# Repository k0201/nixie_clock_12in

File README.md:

# nixie_clock_12in
KiCad hardware project for IN12 lamps

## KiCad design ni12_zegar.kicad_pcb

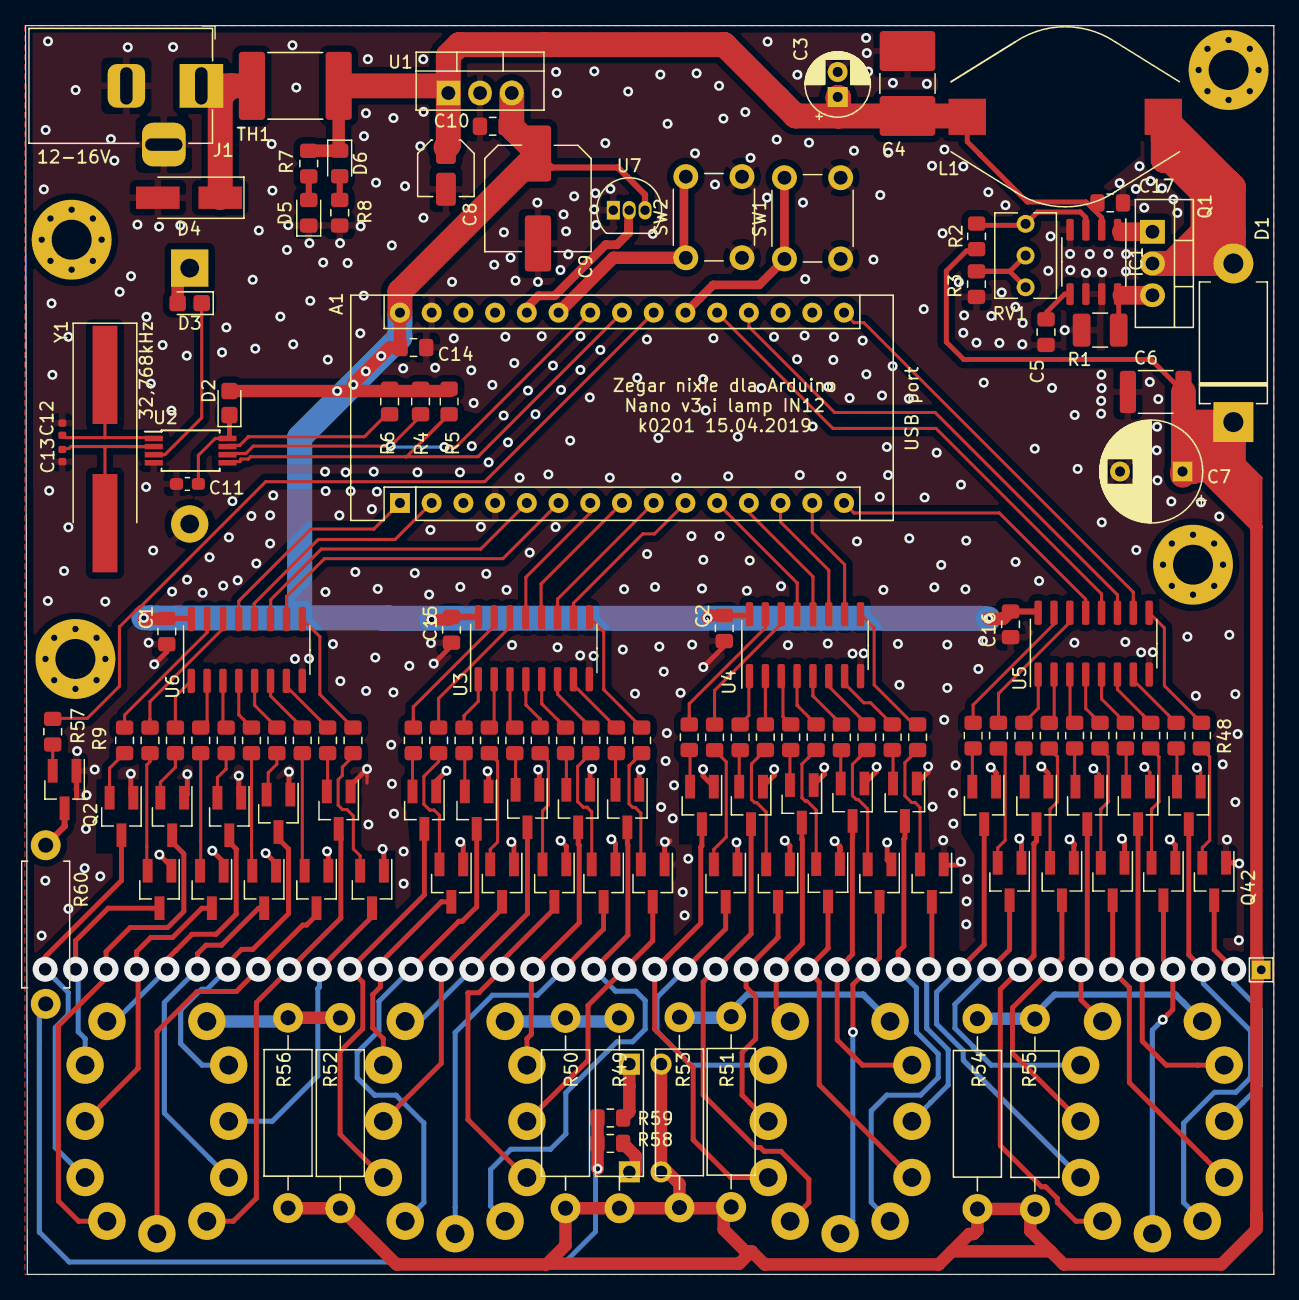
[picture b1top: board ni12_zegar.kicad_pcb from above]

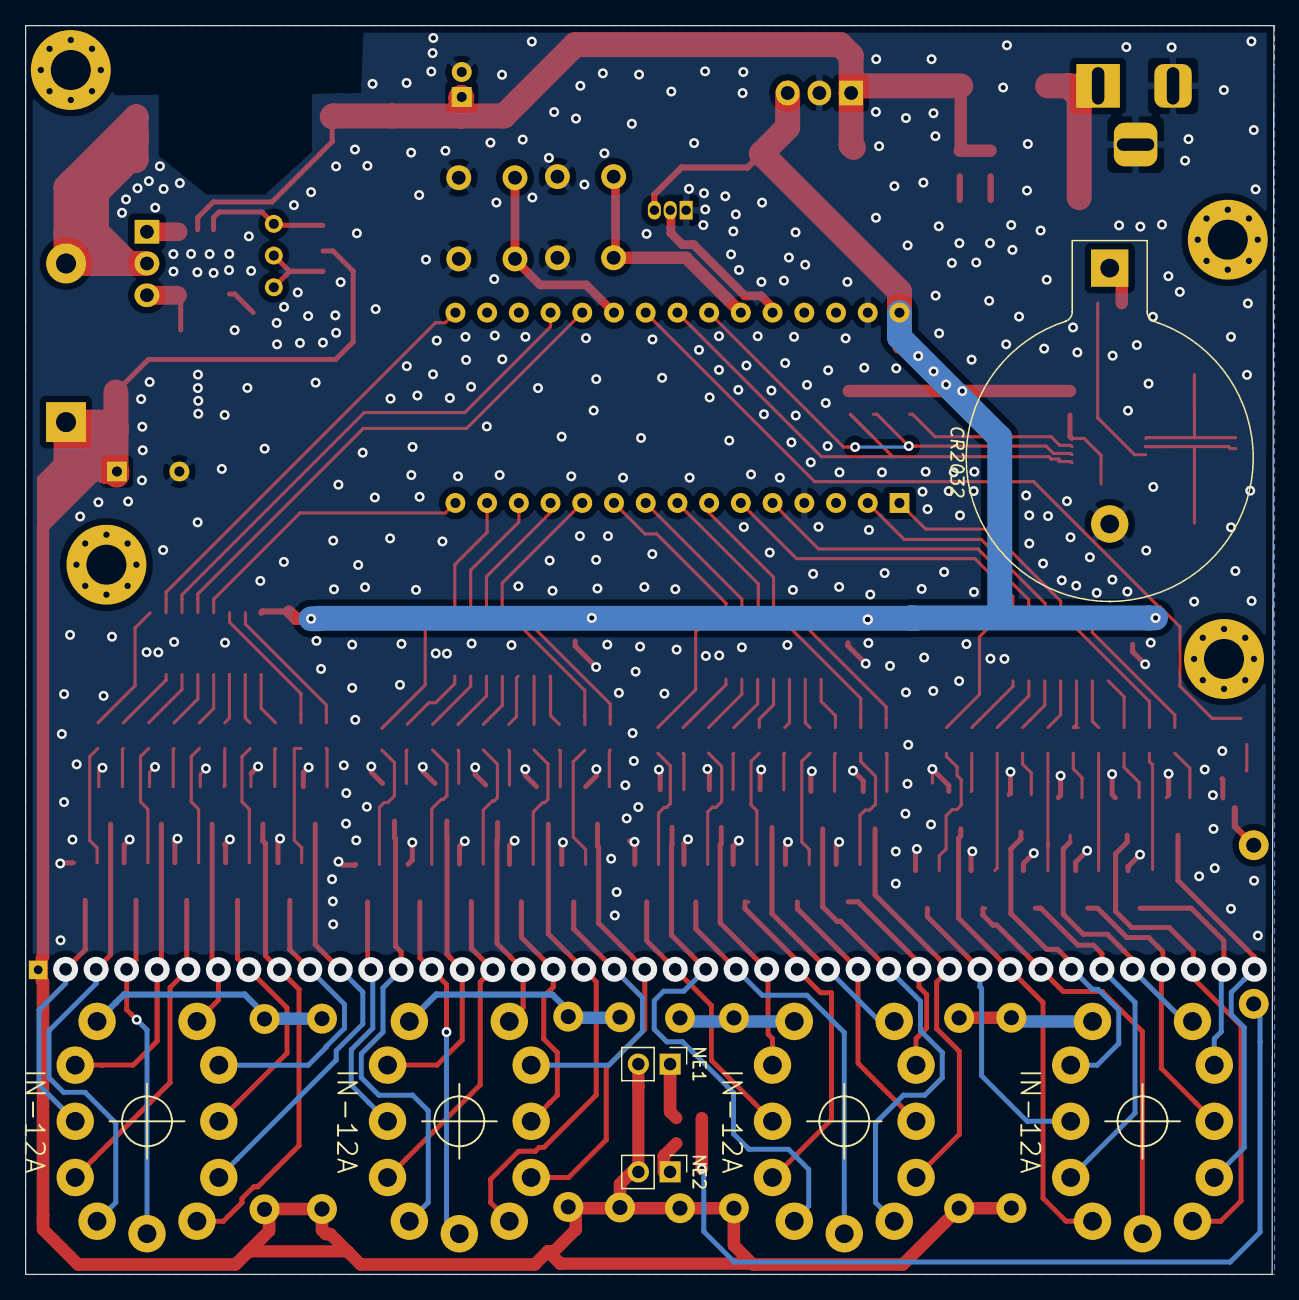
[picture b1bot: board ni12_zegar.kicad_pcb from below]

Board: 2 copper layers, 100.0 x 100.0 mm, 153 parts (7 on the bottom side), 170 nets.

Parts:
A1: Arduino_Nano_v3.x; Arduino_Nano
BT1: Battery_Cell; BatteryHolder_Keystone_103_1x20mm
C1, C2, C5, C10, C14, C15, C16, C17: 100n; C_0805_2012Metric_Pad1.15x1.40mm_HandSolder
C3: 100u; CP_Radial_D5.0mm_P2.00mm
C4: 100n; C_2816_7142Metric_Pad3.20x4.45mm_HandSolder
C6: 100n; C_1812_4532Metric_Pad1.30x3.40mm_HandSolder
C7: 4.7u; CP_Radial_D8.0mm_P5.00mm
C8: 4.7u; C_Elec_4x5.4
C9: 1000u; C_Elec_8x10.2
C11: 100nF; C_0603_1608Metric_Pad1.05x0.95mm_HandSolder
C12, C13: nc; R_0402_1005Metric
D1: D; D_DO-201AD_P12.70mm_Horizontal
D2, D3: 1N4148; D_0805_2012Metric_Castellated
D4: D_TVS; D_SMA_Handsoldering
D5: LED_GREEN; LED_0805_2012Metric_Pad1.15x1.40mm_HandSolder
D6: LED_RED; LED_0805_2012Metric_Pad1.15x1.40mm_HandSolder
H1, H2, H3, H4: MountingHole; MountingHole_3.2mm_M3_Pad_Via
IC1: MAX1771; SO-8_3.9x4.9mm_P1.27mm
J1: Jack-DC; BarrelJack_Horizontal
L1: 100uH; L_Bourns_SDR1806
N1, N2, N3, N4: IN-12A; russian-nixies-IN-12
NE1, NE2: Lamp_Neon; PinHeader_1x02_P2.54mm_Vertical
Q1: IRF740; TO-220-3_Vertical
Q2, Q3, Q4, Q5, Q6, Q7, Q8, Q9, Q10, Q11, Q12, Q13, Q14, Q15, Q16, Q17, Q18, Q19, Q20, Q21, Q22, Q23, Q24, Q25, Q26, Q27, Q28, Q29, Q30, Q31, Q32, Q33, Q34, Q35, Q36, Q37, Q38, Q39, Q40, Q41, Q42: MPSA92; SOT-23_Handsoldering
R1: 50m; R_1210_3225Metric_Pad1.42x2.65mm_HandSolder
R2: 1.5MEG; R_0805_2012Metric_Pad1.15x1.40mm_HandSolder
R3, R6, R9, R10, R11, R12, R13, R14, R15, R16, R17, R18, R19, R20, R21, R22, R23, R24, R25, R26, R27, R28, R29, R30, R31, R32, R33, R34, R35, R36, R37, R38, R39, R40, R41, R42, R43, R44, R45, R46, R47, R48, R57: 10k; R_0805_2012Metric_Pad1.15x1.40mm_HandSolder
R4, R5: 2.2k; R_0805_2012Metric_Pad1.15x1.40mm_HandSolder
R7, R8: 470; R_0805_2012Metric_Pad1.15x1.40mm_HandSolder
R49, R50, R51, R52, R53, R54, R55, R56: 30k; R_Axial_DIN0411_L9.9mm_D3.6mm_P15.24mm_Horizontal
R58, R59: 430k; R_0805_2012Metric_Pad1.15x1.40mm_HandSolder
R60: 0; R_Axial_DIN0411_L9.9mm_D3.6mm_P12.70mm_Horizontal
RV1: 10k; Potentiometer_Vishay_T73XW_Horizontal
SW1, SW2: SW_Push; SW_PUSH_6mm_H5mm
TH1: Thermistor_PTC; Fuse_2920_7451Metric_Pad2.10x5.45mm_HandSolder
TP1: TestPoint; TestPoint_THTPad_1.5x1.5mm_Drill0.7mm
U1: L7805; TO-220-3_Vertical
U2: MCP7940N-xST; TSSOP-8_4.4x3mm_P0.65mm
U3, U4, U5, U6: 4028; SOIC-16_3.9x9.9mm_P1.27mm
U7: LM35-LP; TO-92_Inline
Y1: 32,768kHz; Crystal_SMD_HC49-SD_HandSoldering

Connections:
/5V: A1.30, C1.1, C2.1, C9.1, C10.1, C14.1, C15.1, C16.1, D2.2, R4.1, R5.1, R6.1, U1.3, U3.16, U4.16, U5.16, U6.16, U7.3
/12V: C3.1, C4.1, C8.1, C17.2, D6.1, IC1.2, L1.1, R7.1, TH1.1, U1.1
/A1: A1.6, U6.10
/A2: A1.10, U3.10
/A3: A1.14, U4.10
/A4: A1.16, U5.10
/B1: A1.1, U6.13
/B2: A1.7, U3.13
/B3: A1.11, U4.13
/B4: A1.15, U5.13
/C1: A1.2, U6.12
/C2: A1.8, U3.12
/C3: A1.12, U4.12
/C4: A1.20, U5.12
/D1: A1.5, U6.11
/D2: A1.9, U3.11
/D3: A1.13, U4.11
/D4: A1.19, U5.11
/DZIESIATKI GODZIN/200V: C6.2, C7.1, D1.1, NE1.2, NE2.2, R2.1, R49.1, R50.2, R51.1, R52.2, R53.2, R54.1, R55.2, R56.1, TP1.1
/SCL: A1.24, R4.2, U2.6
/SDA: A1.23, R5.2, U2.5
/neon: A1.22, R57.2
/rtc/MPF: R6.2, U2.7
/sw1: A1.25, SW2.1
/sw2: A1.21, SW1.1
/temp: A1.26, U7.2
GND: A1.4, A1.29, BT1.2, C1.2, C2.2, C3.2, C4.2, C5.2, C6.1, C7.2, C8.2, C9.2, C10.2, C11.2, C12.1, C13.1, C14.2, C15.2, C16.2, C17.1, D4.2, D5.1, IC1.4, IC1.6, IC1.7, J1.2, J1.e3, Q2.1, Q3.1, Q4.1, Q5.1, Q6.1, Q7.1, Q8.1, Q9.1, Q10.1, Q11.1, Q12.1, Q13.1, Q14.1, Q15.1, Q16.1, Q17.1, Q18.1, Q19.1, Q20.1, Q21.1, Q22.1, Q23.1, Q24.1, Q25.1, Q26.1, Q27.1, Q28.1, Q29.1, Q30.1, Q31.1, Q32.1, Q33.1, Q34.1, Q35.1, Q36.1, Q37.1, Q38.1, Q39.1, Q40.1, Q41.1, Q42.1, R1.2, R3.2, R8.2, SW1.2, SW2.2, U1.2, U2.4, U3.8, U4.8, U5.8, U6.8, U7.1
unnamed: BT1.1, D3.2
unnamed: C5.1, IC1.5
unnamed: C11.1, D2.1, U2.8
unnamed: C12.2, U2.1, Y1.1
unnamed: C13.2, U2.2, Y1.2
unnamed: D1.2, L1.2, Q1.2
unnamed: D3.1, U2.3
unnamed: D4.1, J1.1, TH1.2
unnamed: D5.2, R7.2
unnamed: D6.2, R8.1
unnamed: IC1.1, Q1.1
unnamed: IC1.3, R2.2, RV1.3
unnamed: IC1.8, Q1.3, R1.1
unnamed: N1.0, Q11.3
unnamed: N1.1, Q2.3
unnamed: N1.2, Q3.3
unnamed: N1.3, Q4.3
unnamed: N1.4, Q5.3
unnamed: N1.5, Q6.3
unnamed: N1.6, Q7.3
unnamed: N1.7, Q8.3
unnamed: N1.8, Q9.3
unnamed: N1.9, Q10.3
unnamed: N1.A, R49.2, R50.1
unnamed: N2.0, Q21.3
unnamed: N2.1, Q12.3
unnamed: N2.2, Q13.3
unnamed: N2.3, Q14.3
unnamed: N2.4, Q15.3
unnamed: N2.5, Q16.3
unnamed: N2.6, Q17.3
unnamed: N2.7, Q18.3
unnamed: N2.8, Q19.3
unnamed: N2.9, Q20.3
unnamed: N2.A, R51.2, R53.1
unnamed: N3.0, Q31.3
unnamed: N3.1, Q22.3
unnamed: N3.2, Q23.3
unnamed: N3.3, Q24.3
unnamed: N3.4, Q25.3
unnamed: N3.5, Q26.3
unnamed: N3.6, Q27.3
unnamed: N3.7, Q28.3
unnamed: N3.8, Q29.3
unnamed: N3.9, Q30.3
unnamed: N3.A, R54.2, R55.1
unnamed: N4.0, Q41.3
unnamed: N4.1, Q32.3
unnamed: N4.2, Q33.3
unnamed: N4.3, Q34.3
unnamed: N4.4, Q35.3
unnamed: N4.5, Q36.3
unnamed: N4.6, Q37.3
unnamed: N4.7, Q38.3
unnamed: N4.8, Q39.3
unnamed: N4.9, Q40.3
unnamed: N4.A, R52.1, R56.2
unnamed: NE1.1, R58.2
unnamed: NE2.1, R59.2
unnamed: Q2.2, R9.1
unnamed: Q3.2, R10.1
unnamed: Q4.2, R11.1
unnamed: Q5.2, R12.1
unnamed: Q6.2, R13.1
unnamed: Q7.2, R14.1
unnamed: Q8.2, R15.1
unnamed: Q9.2, R16.1
unnamed: Q10.2, R17.1
unnamed: Q11.2, R18.1
unnamed: Q12.2, R19.1
unnamed: Q13.2, R20.1
unnamed: Q14.2, R21.1
unnamed: Q15.2, R22.1
unnamed: Q16.2, R23.1
unnamed: Q17.2, R24.1
unnamed: Q18.2, R25.1
unnamed: Q19.2, R26.1
unnamed: Q20.2, R27.1
unnamed: Q21.2, R28.1
unnamed: Q22.2, R29.1
unnamed: Q23.2, R30.1
unnamed: Q24.2, R31.1
unnamed: Q25.2, R32.1
unnamed: Q26.2, R33.1
unnamed: Q27.2, R34.1
unnamed: Q28.2, R35.1
unnamed: Q29.2, R36.1
unnamed: Q30.2, R37.1
unnamed: Q31.2, R38.1
unnamed: Q32.2, R39.1
unnamed: Q33.2, R40.1
unnamed: Q34.2, R41.1
unnamed: Q35.2, R42.1
unnamed: Q36.2, R43.1
unnamed: Q37.2, R44.1
unnamed: Q38.2, R45.1
unnamed: Q39.2, R46.1
unnamed: Q40.2, R47.1
unnamed: Q41.2, R48.1
unnamed: Q42.2, R57.1
unnamed: Q42.3, R60.2
unnamed: R3.1, RV1.1, RV1.2
unnamed: R9.2, U3.3
unnamed: R10.2, U3.14
unnamed: R11.2, U3.2
unnamed: R12.2, U3.15
unnamed: R13.2, U3.1
unnamed: R14.2, U3.6
unnamed: R15.2, U3.7
unnamed: R16.2, U3.4
unnamed: R17.2, U3.9
unnamed: R18.2, U3.5
unnamed: R19.2, U4.3
unnamed: R20.2, U4.14
unnamed: R21.2, U4.2
unnamed: R22.2, U4.15
unnamed: R23.2, U4.1
unnamed: R24.2, U4.6
unnamed: R25.2, U4.7
unnamed: R26.2, U4.4
unnamed: R27.2, U4.9
unnamed: R28.2, U4.5
unnamed: R29.2, U5.3
unnamed: R30.2, U5.14
unnamed: R31.2, U5.2
unnamed: R32.2, U5.15
unnamed: R33.2, U5.1
unnamed: R34.2, U5.6
unnamed: R35.2, U5.7
unnamed: R36.2, U5.4
unnamed: R37.2, U5.9
unnamed: R38.2, U5.5
unnamed: R39.2, U6.3
unnamed: R40.2, U6.14
unnamed: R41.2, U6.2
unnamed: R42.2, U6.15
unnamed: R43.2, U6.1
unnamed: R44.2, U6.6
unnamed: R45.2, U6.7
unnamed: R46.2, U6.4
unnamed: R47.2, U6.9
unnamed: R48.2, U6.5
unnamed: R58.1, R59.1, R60.1

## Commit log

2019-04-17 Add files via upload
    first commit of rev 1
2019-06-16 małe poprawki podczas montażu
2019-06-22 drobne poprawki
2019-06-26 dodanie pdf schematu
